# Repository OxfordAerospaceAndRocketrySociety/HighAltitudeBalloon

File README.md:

# HighAltitudeBalloon
A raspberry pi pico based GPS tracker and reciever for high altitude ballooning.

Please read [Setup.md](https://github.com/OxfordAerospaceAndRocketrySociety/HighAltitudeBalloon/blob/main/Setup.md) for instructions on installing the dependencies.

Please also have a look at [TODO.md](https://github.com/OxfordAerospaceAndRocketrySociety/HighAltitudeBalloon/blob/main/TODO.md) for infomation about what is yet to be done!

To build your own please see [Wiring.md](https://github.com/OxfordAerospaceAndRocketrySociety/HighAltitudeBalloon/blob/main/Wiring.md), it has a table of all of the connections nececary.

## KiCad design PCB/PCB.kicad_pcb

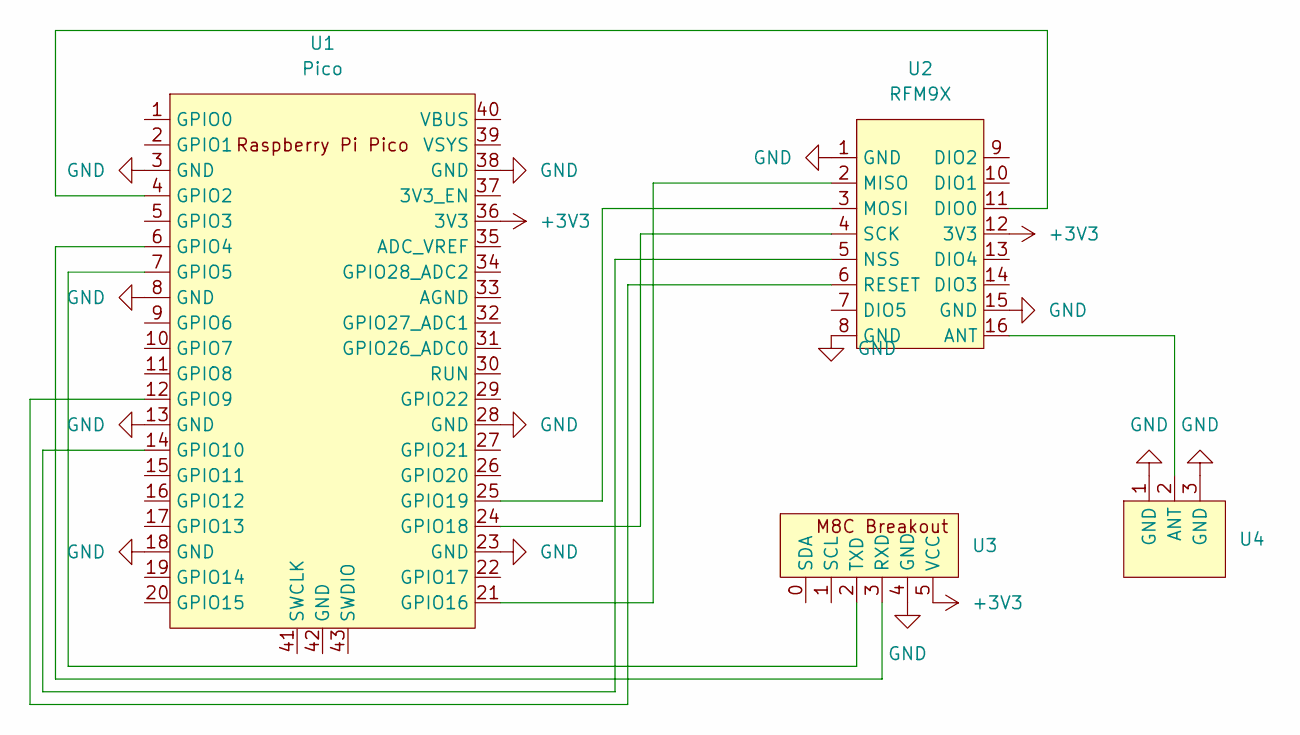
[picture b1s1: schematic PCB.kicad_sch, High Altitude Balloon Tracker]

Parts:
U1: Pico; RPi_Pico_SMD_TH
U2: RFM9X
U3: M8C Pico Breakout
U4: Antenna

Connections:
+3V3: U1.36 (3V3), U2.12 (3V3), U3.5 (VCC)
GND: U1.3 (GND), U1.8 (GND), U1.13 (GND), U1.18 (GND), U1.23 (GND), U1.28 (GND), U1.38 (GND), U2.1 (GND), U2.8 (GND), U2.15 (GND), U3.4 (GND), U4.1 (GND), U4.3 (GND)
unnamed: U1.4 (GPIO2), U2.11 (DIO0)
unnamed: U1.6 (GPIO4), U3.3 (RXD)
unnamed: U1.7 (GPIO5), U3.2 (TXD)
unnamed: U1.12 (GPIO9), U2.6 (RESET)
unnamed: U1.14 (GPIO10), U2.5 (NSS)
unnamed: U1.21 (GPIO16), U2.2 (MISO)
unnamed: U1.24 (GPIO18), U2.4 (SCK)
unnamed: U1.25 (GPIO19), U2.3 (MOSI)
unnamed: U2.16 (ANT), U4.2 (ANT)

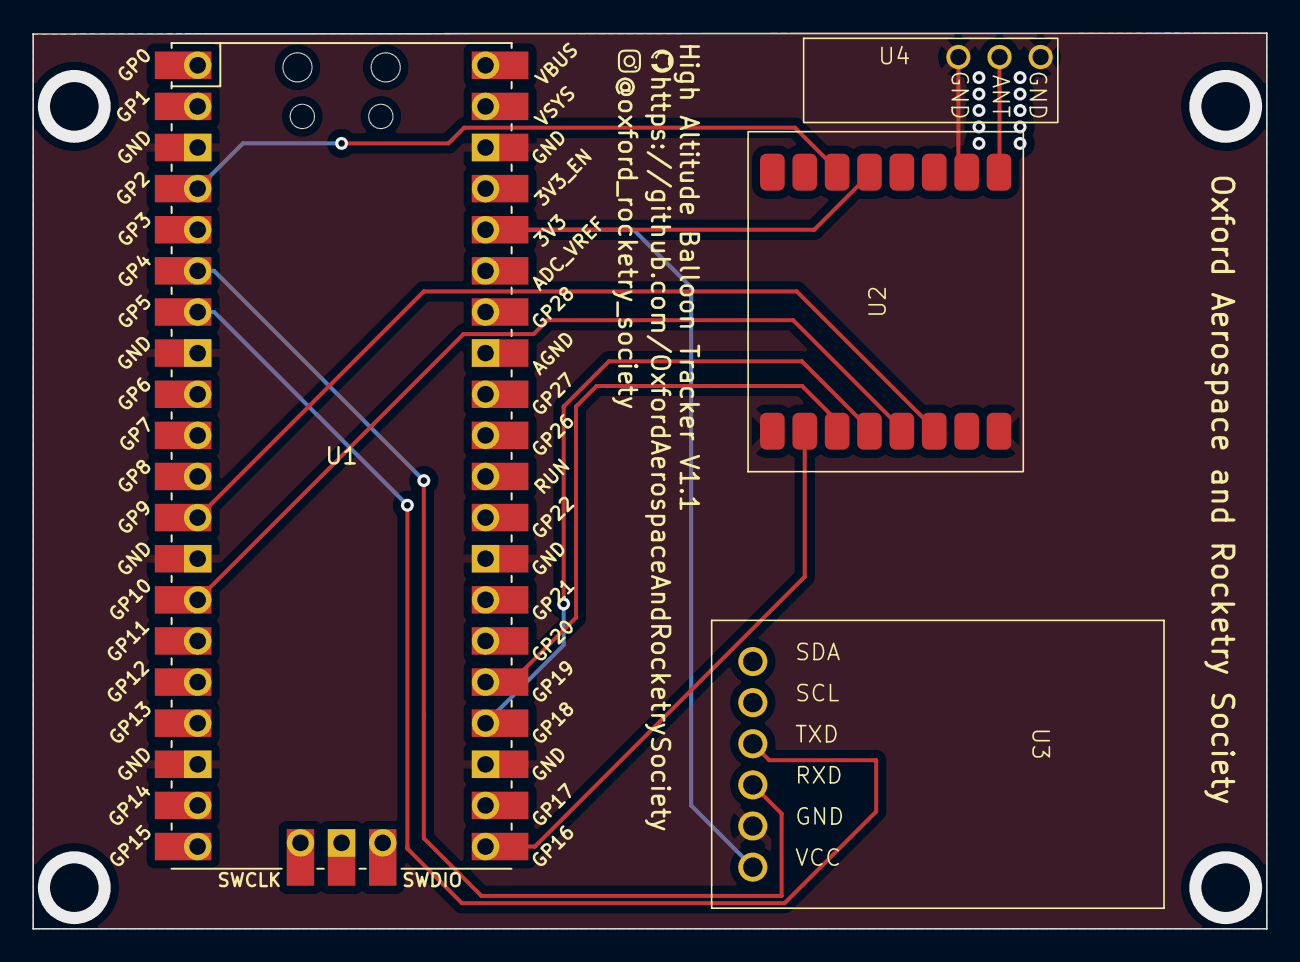
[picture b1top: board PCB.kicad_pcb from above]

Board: 2 copper layers, 76.2 x 55.3 mm, 4 parts (0 on the bottom side), 11 nets.

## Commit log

2024-05-13 Added Parts and TODO lists
2024-06-11 Added files for GPS tests
    Arduino programs for testing the UBLOX GPS module on the raspberry pi pico
2024-06-11 Added setup code for GPS (not working)
2024-06-12 Remove outdated pre-compiled files
2024-06-12 Add a setup guide
2024-06-13 Code for formatting GPS data as UKHAS message
    See GPSTest2
2024-06-13 Tidy up the build folders
2024-07-04 Test out LoRa Modules
    Also added some additional documentation for wiring the pico
2024-07-04 Added serial reader software for PC
2024-07-05 Added python script with map
2024-07-06 Added a V1 of the tracker PCB
2024-07-07 Added gerber files for PCB
2024-07-13 Add main tracker code
2024-07-22 Added LED Error Codes
2024-07-25 Added time to no fix message
2024-07-25 Updated PCB to use SMT RFM9X
    PCB now on v1.1, currently untested
2024-07-31 Updated code for correct checksum
2024-08-06 Desktop program can now upload to sondehub
2024-08-07 Quick fix for corrupted CRCs
2024-08-09 Tidy up some code
2024-08-12 serialRead.py bugfixes
2024-09-15 Added antenna mount CAD
2024-09-26 Create LaptoplessTest0
    Folder for Receiver and Transmitter code, modified to be tested without a laptop (Because my laptop battery doesnt work)
